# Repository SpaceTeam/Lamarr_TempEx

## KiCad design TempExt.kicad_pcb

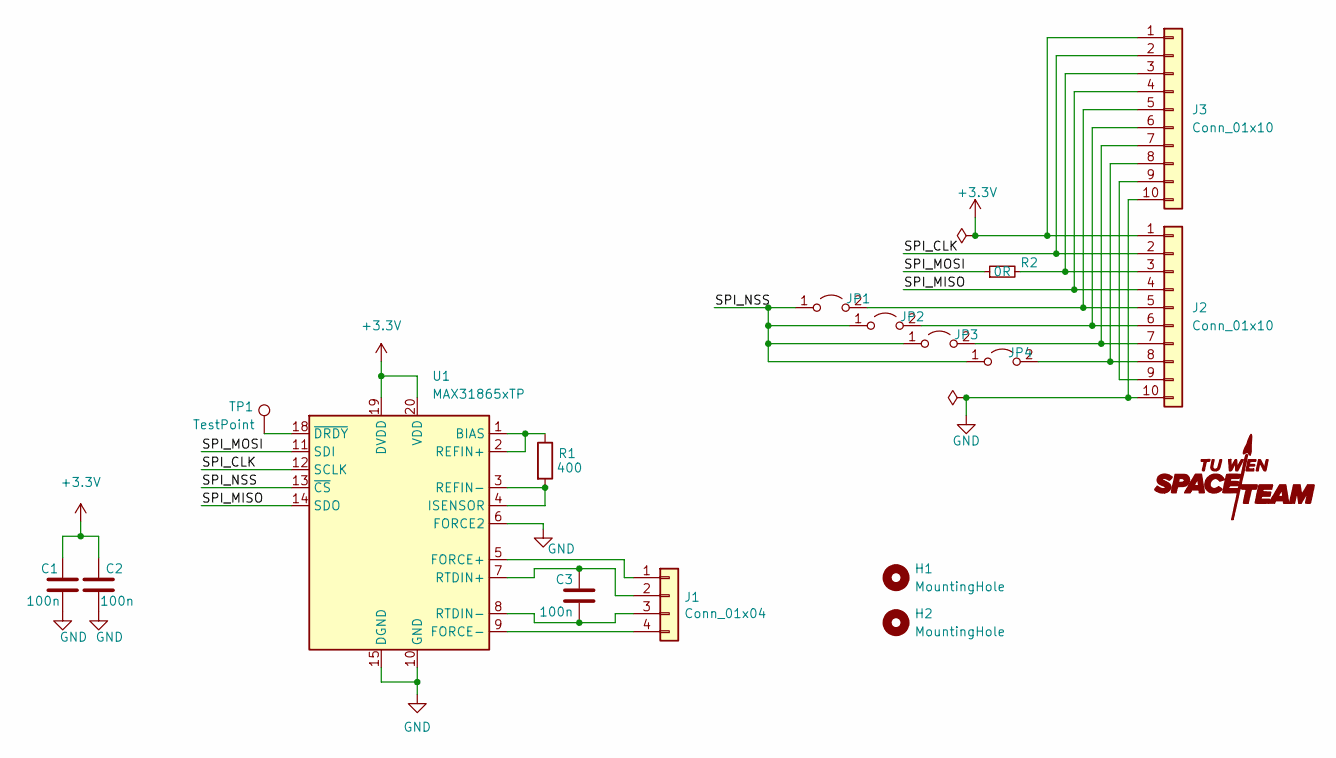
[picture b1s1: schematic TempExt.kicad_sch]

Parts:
C1, C2, C3: 100n; C_0603_1608Metric_Pad1.08x0.95mm_HandSolder
G1: SpaceTeam_LOGO; ST_Logo_new
H1, H2: MountingHole; MountingHole_2.1mm
J1: Conn_01x04; TE_M12_4_Pin_PCB
J2, J3: Conn_01x10; IDC-Header_2x05_P2.54mm_Vertical
JP1, JP2, JP3, JP4: Jumper_2_Open; SolderJumper-2_P1.3mm_Open_RoundedPad1.0x1.5mm
R1: 400; R_0603_1608Metric_Pad0.98x0.95mm_HandSolder
R2: 0R; R_0805_2012Metric
TP1: TestPoint; TestPoint_THTPad_D1.0mm_Drill0.5mm
U1: MAX31865xTP; TQFN-20-1EP_5x5mm_P0.65mm_EP3.25x3.25mm

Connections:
+3V3: C1.1, C2.1, J2.1, J3.1, U1.19 (DVDD), U1.20 (VDD)
/SPI_CLK: J2.2, J3.2, U1.12 (SCLK)
/SPI_MISO: J2.4, J3.4, U1.14 (SDO)
/SPI_MOSI: R2.1, U1.11 (SDI)
/SPI_NSS: JP1.1 (A), JP2.1 (A), JP3.1 (A), JP4.1 (A), U1.13 (~CS)
GND: C1.2, C2.2, J2.10, J3.10, U1.6 (FORCE2), U1.10 (GND), U1.15 (DGND), U1.16 (GND), U1.21 (GND)
unnamed: C3.2, J1.3, U1.8 (RTDIN-)
unnamed: J2.3, J3.3, R2.2
unnamed: J2.5, J3.5, JP1.2 (B)
unnamed: J2.6, J3.6, JP2.2 (B)
unnamed: J2.7, J3.7, JP3.2 (B)
unnamed: J2.8, J3.8, JP4.2 (B)
unnamed: J2.9, J3.9
unnamed: R1.1, U1.1 (BIAS), U1.2 (REFIN+)
unnamed: R1.2, U1.3 (REFIN-), U1.4 (ISENSOR)
unnamed: J1.1, U1.5 (FORCE+)
unnamed: C3.1, J1.2, U1.7 (RTDIN+)
unnamed: J1.4, U1.9 (FORCE-)
unnamed: TP1.1, U1.18 (~DRDY)

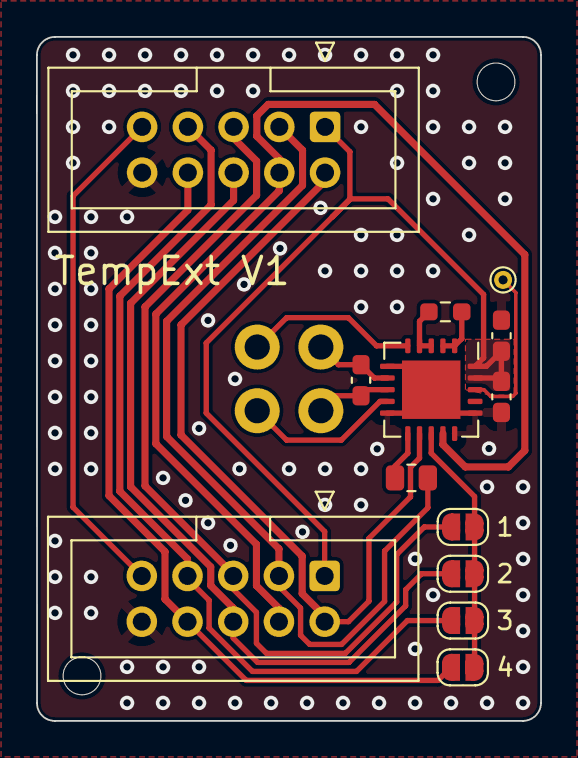
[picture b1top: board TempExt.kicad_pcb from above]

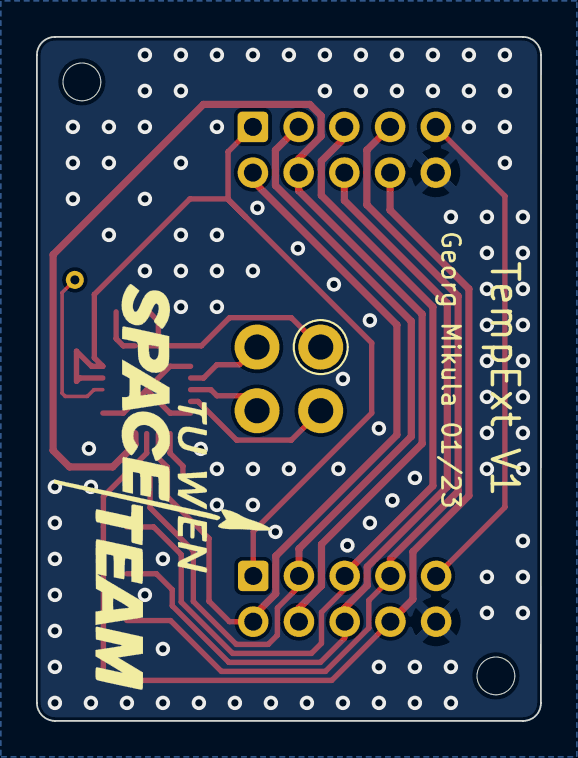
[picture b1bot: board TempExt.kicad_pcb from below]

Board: 2 copper layers, 28.0 x 38.0 mm, 17 parts (4 on the bottom side), 19 nets.

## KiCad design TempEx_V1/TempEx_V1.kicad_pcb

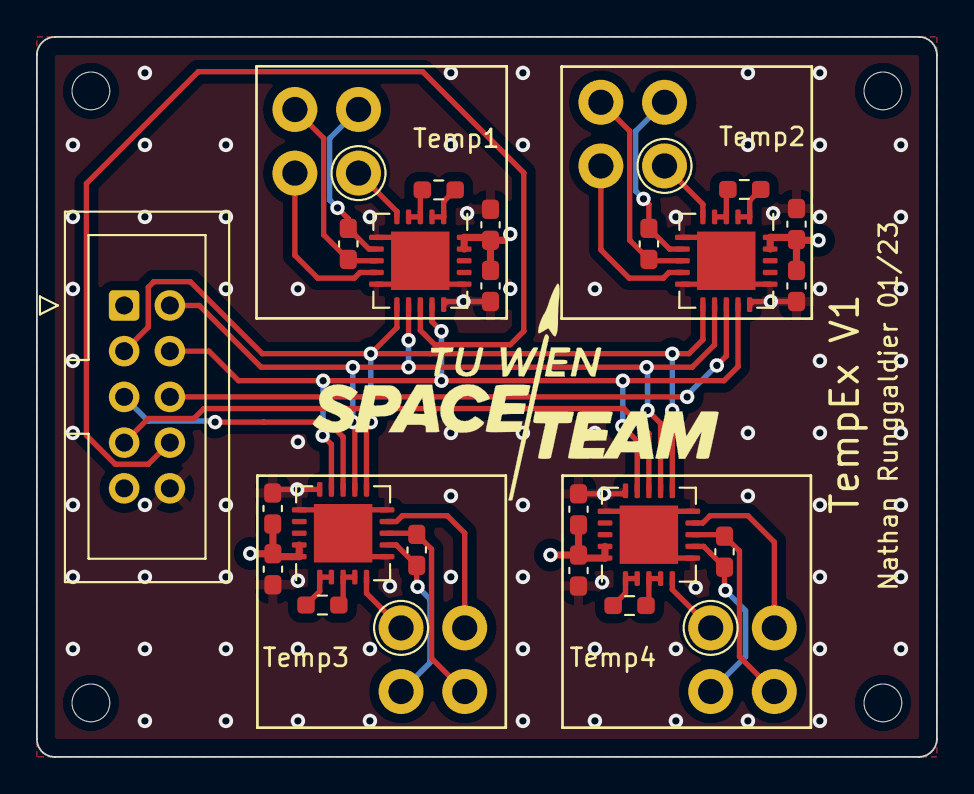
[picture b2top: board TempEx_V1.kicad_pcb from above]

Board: 4 copper layers, 50.0 x 40.0 mm, 30 parts (0 on the bottom side), 33 nets.

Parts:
C1, C2, C3, C4, C5, C6, C7, C8, C9, C10, C11, C12: 100n; C_0603_1608Metric_Pad1.08x0.95mm_HandSolder
G1: SpaceTeam_LOGO; ST_Logo_new
H1, H2, H3, H4: MountingHole; MountingHole_2.1mm
J1, J3, J4, J5: Conn_01x04; TE_M12_4_Pin_PCB
J2: Conn_01x10; IDC-Header_2x05_P2.54mm_Vertical
R1, R2, R3, R4: 400; R_0603_1608Metric_Pad0.98x0.95mm_HandSolder
U1, U2, U3, U4: MAX31865xTP; TQFN-20-1EP_5x5mm_P0.65mm_EP3.25x3.25mm

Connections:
+3V3: C1.1, C2.1, C4.1, C5.1, C7.1, C8.1, C10.1, C11.1, J2.1, U1.19 (DVDD), U1.20 (VDD), U2.19 (DVDD), U2.20 (VDD), U3.19 (DVDD), U3.20 (VDD), U4.19 (DVDD), U4.20 (VDD)
/SPI_CLK: J2.2, U1.12 (SCLK), U2.12 (SCLK), U3.12 (SCLK), U4.12 (SCLK)
/SPI_MISO: J2.4, U1.14 (SDO), U2.14 (SDO), U3.14 (SDO), U4.14 (SDO)
/SPI_MOSI: J2.3, U1.11 (SDI), U2.11 (SDI), U3.11 (SDI), U4.11 (SDI)
/SPI_NSS1: J2.5, U3.13 (~CS)
/SPI_NSS2: J2.6, U2.13 (~CS)
/SPI_NSS3: J2.7, U4.13 (~CS)
/SPI_NSS4: J2.8, U1.13 (~CS)
GND: C1.2, C2.2, C4.2, C5.2, C7.2, C8.2, C10.2, C11.2, J2.10, U1.6 (FORCE2), U1.10 (GND), U1.15 (DGND), U1.16 (GND), U1.21 (GND), U2.6 (FORCE2), U2.10 (GND), U2.15 (DGND), U2.16 (GND), U2.21 (GND), U3.6 (FORCE2), U3.10 (GND), U3.15 (DGND), U3.16 (GND), U3.21 (GND), U4.6 (FORCE2), U4.10 (GND), U4.15 (DGND), U4.16 (GND), U4.21 (GND)
unnamed: C3.1, J1.2, U1.7 (RTDIN+)
unnamed: C3.2, J1.3, U1.8 (RTDIN-)
unnamed: C6.1, J3.2, U2.7 (RTDIN+)
unnamed: C6.2, J3.3, U2.8 (RTDIN-)
unnamed: C9.1, J4.2, U3.7 (RTDIN+)
unnamed: C9.2, J4.3, U3.8 (RTDIN-)
unnamed: C12.1, J5.2, U4.7 (RTDIN+)
unnamed: C12.2, J5.3, U4.8 (RTDIN-)
unnamed: J1.1, U1.5 (FORCE+)
unnamed: J1.4, U1.9 (FORCE-)
unnamed: J3.1, U2.5 (FORCE+)
unnamed: J3.4, U2.9 (FORCE-)
unnamed: J4.1, U3.5 (FORCE+)
unnamed: J4.4, U3.9 (FORCE-)
unnamed: J5.1, U4.5 (FORCE+)
unnamed: J5.4, U4.9 (FORCE-)
unnamed: R1.1, U1.1 (BIAS), U1.2 (REFIN+)
unnamed: R1.2, U1.3 (REFIN-), U1.4 (ISENSOR)
unnamed: R2.1, U2.1 (BIAS), U2.2 (REFIN+)
unnamed: R2.2, U2.3 (REFIN-), U2.4 (ISENSOR)
unnamed: R3.1, U3.1 (BIAS), U3.2 (REFIN+)
unnamed: R3.2, U3.3 (REFIN-), U3.4 (ISENSOR)
unnamed: R4.1, U4.1 (BIAS), U4.2 (REFIN+)
unnamed: R4.2, U4.3 (REFIN-), U4.4 (ISENSOR)

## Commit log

2022-12-21 GNDD Problem still unresolved
2022-12-23 Stitching missing
2022-12-23 Updated GND
    All GNDD switched to GND
2022-12-30 Change from 2 layers to 4
2023-01-03 Layer change + 4 pin setup + stitching
2023-01-08 New Layout changed back to 2 layers
